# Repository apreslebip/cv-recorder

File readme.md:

## Knob recorder :v:
:warning: **UNDER DEV ARDUINO CODE**

As you push a **button**, you can move the pot and it will record your movements for some time... As soon as you release the **button**, **out** give a loop of the recorded CV.
A clock in **reset** will reset the loop.

I did mine 1u. I'll post pics.

:phone:  www.instagram.com/apres.lebip/

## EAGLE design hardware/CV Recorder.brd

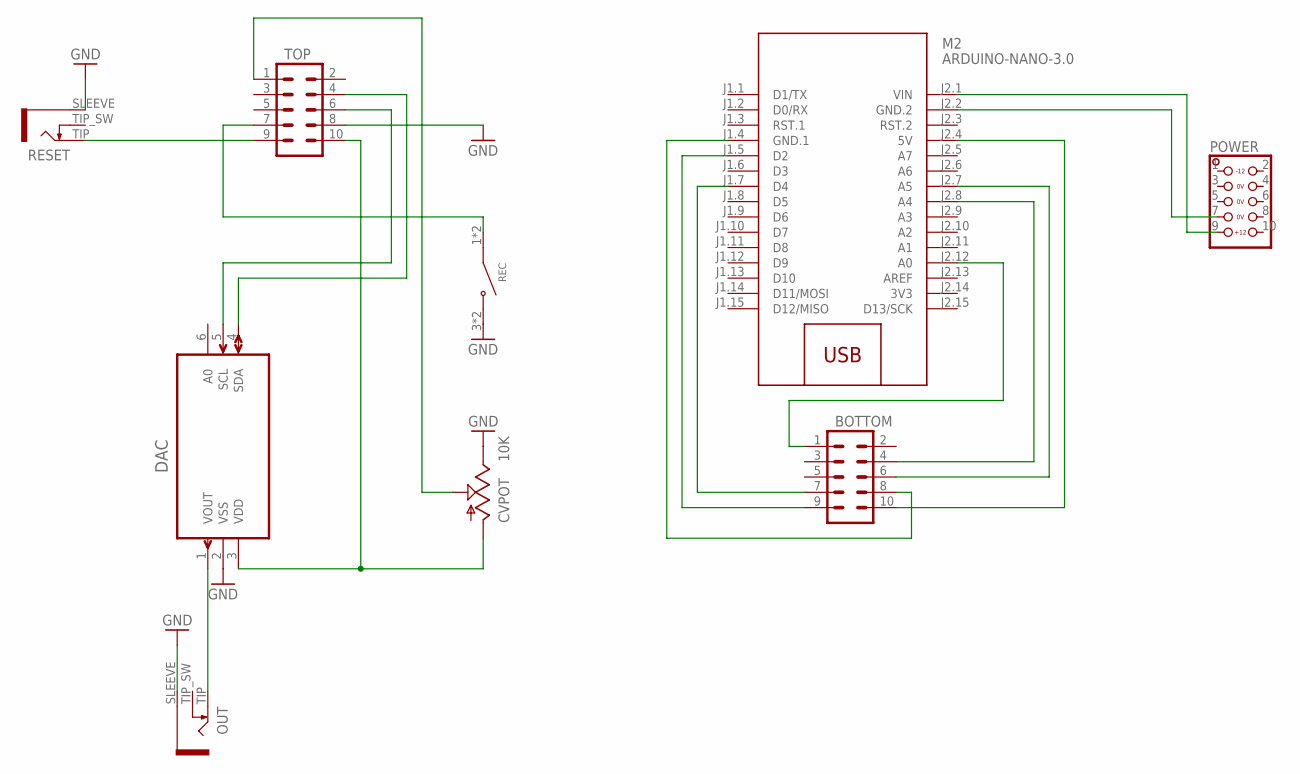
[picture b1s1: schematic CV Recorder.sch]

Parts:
BOTTOM: M05X2PTH; 2X5
CVPOT: 10K; ALPS_POT
DAC: MCP4725A0T-E/CH; SOT95P270X145-6N
M2: ARDUINO-NANO-3.0
OUT: JACK-3_5MM-MONO-SW-ALT; WQP_PJ301M_ALT
POWER: EUROPWR_2X05-OPEN; 2X05_EUROPWR_OPEN
REC: D6R90_F1_LFS; SW_D6R90_F1_LFS
RESET: JACK-3_5MM-MONO-SW-ALT; WQP_PJ301M_ALT
TOP: M05X2PTH; 2X5

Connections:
3V3: M2.J2.14 (3V3)
GND: CVPOT.P$1 (3), DAC.2 (VSS), OUT.SLEEVE, REC.3 (NO), REC.4 (NO), RESET.SLEEVE, TOP.8
unnamed: M2.J2.1 (VIN), POWER.9
unnamed: M2.J2.2 (GND.2), POWER.7
unnamed: DAC.1 (VOUT), OUT.TIP
unnamed: CVPOT.P$3 (1), DAC.3 (VDD), TOP.10
unnamed: RESET.TIP, TOP.9
unnamed: REC.1 (COM), REC.2 (COM), TOP.7
unnamed: CVPOT.P$2 (2), TOP.1
unnamed: DAC.5 (SCL), TOP.6
unnamed: BOTTOM.10, M2.J2.4 (5V)
unnamed: BOTTOM.8, M2.J1.4 (GND.1)
unnamed: BOTTOM.6, M2.J2.7 (A5)
unnamed: BOTTOM.4, M2.J2.8 (A4)
unnamed: BOTTOM.1, M2.J2.12 (A0)
unnamed: BOTTOM.7, M2.J1.7 (D4)
unnamed: DAC.4 (SDA), TOP.4
unnamed: BOTTOM.9, M2.J1.5 (D2)

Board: 2 copper layers, 9 parts (3 on the bottom side), 17 nets, no tracks yet.

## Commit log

2021-06-07 Adding DAC implementation for A
2021-06-07 Adding DAC implementation on A
2021-06-07 Adding DACB implementation
2021-06-07 Reverting to single channel for usability reasons and adding a reset jack
2021-06-08 Adding Eagle schematic and board for hardware 1U

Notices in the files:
parts and their libraries:
diy-modules: Released under the Creative Commons Attribution 4.0 International License: http://creativecommons.org/licenses/by/4.0
